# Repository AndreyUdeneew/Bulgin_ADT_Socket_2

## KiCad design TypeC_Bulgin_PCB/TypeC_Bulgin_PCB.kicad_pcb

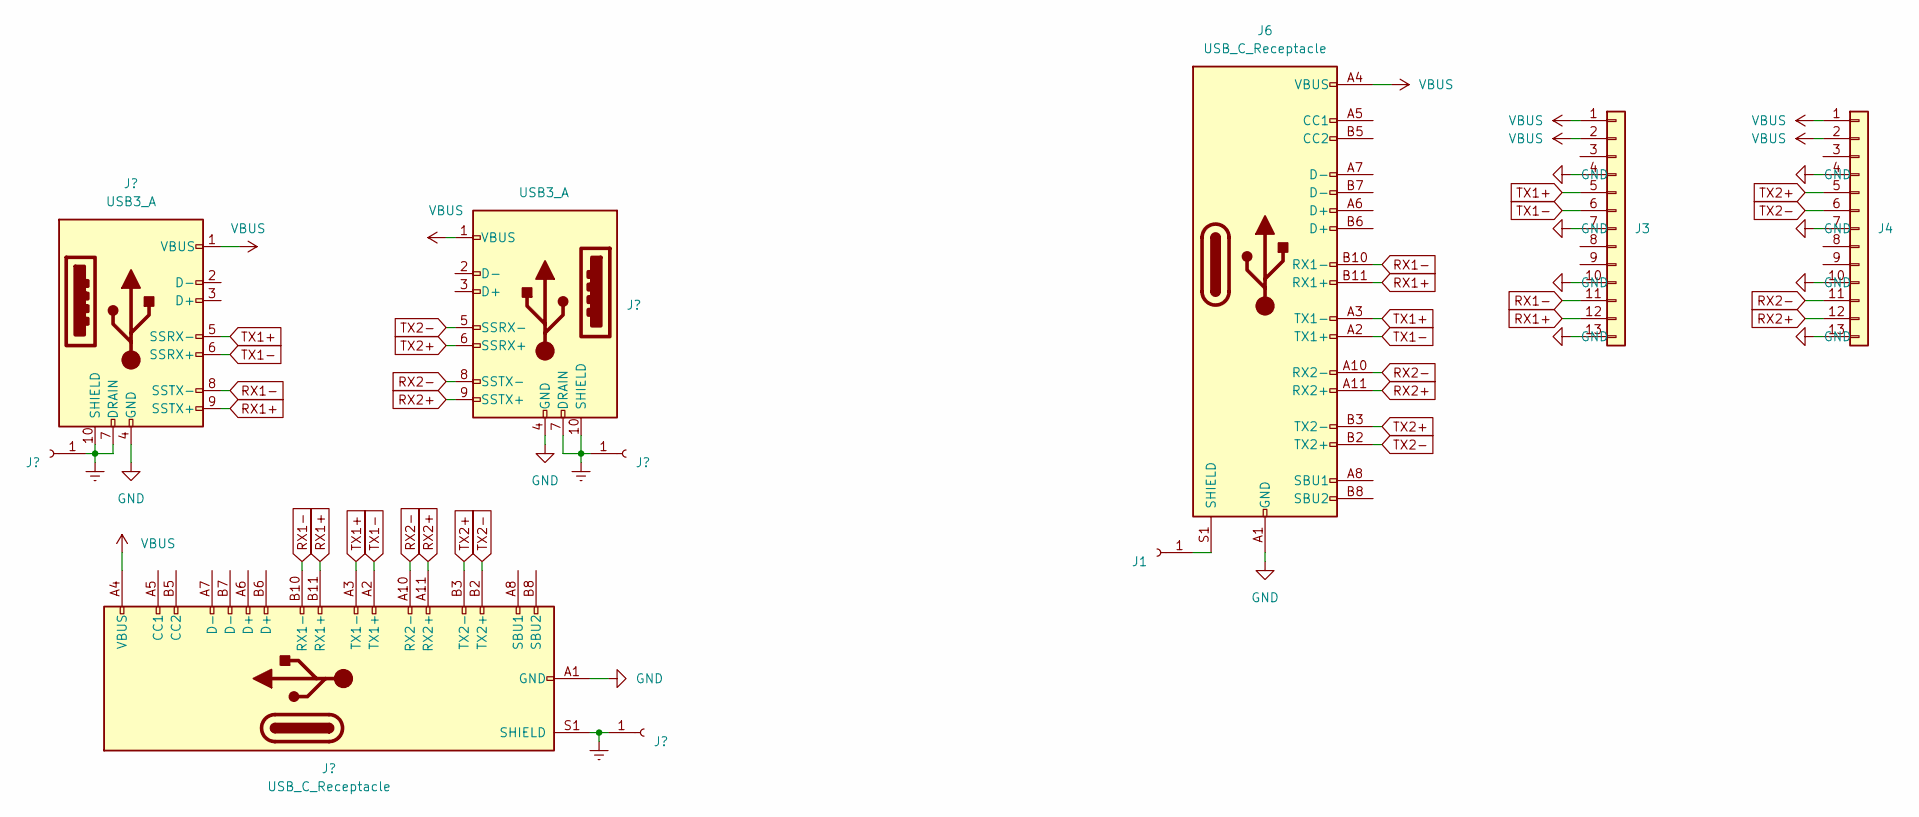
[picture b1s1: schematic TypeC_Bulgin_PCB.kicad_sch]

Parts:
J1: Conn_01x01_Female; PinHeader_1x01_P1.00mm_Vertical
J3, J4: Conn_01x13; ADT_13pin
J6: USB_C_Receptacle; USB_C_Receptacle_JAE_DX07S024WJ3R400

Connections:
GND: J3.4, J3.7, J3.10, J3.13, J4.4, J4.7, J4.10, J4.13, J6.A1 (GND), J6.A12 (GND), J6.B1 (GND), J6.B12 (GND)
unnamed: J1.1, J6.S1 (SHIELD)
RX1+: J3.12, J6.B11 (RX1+)
RX1-: J3.11, J6.B10 (RX1-)
RX2+: J4.12, J6.A11 (RX2+)
RX2-: J4.11, J6.A10 (RX2-)
TX1+: J3.5, J6.A3 (TX1-)
TX1-: J3.6, J6.A2 (TX1+)
TX2+: J4.5, J6.B3 (TX2-)
TX2-: J4.6, J6.B2 (TX2+)
VBUS: J3.1, J3.2, J4.1, J4.2, J6.A4 (VBUS), J6.A9 (VBUS), J6.B4 (VBUS), J6.B9 (VBUS)

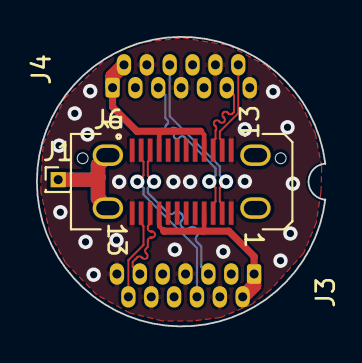
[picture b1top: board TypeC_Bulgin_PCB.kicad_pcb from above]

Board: 2 copper layers, 16.0 x 16.1 mm, 4 parts (0 on the bottom side), 11 nets.

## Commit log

2022-06-03 v0.1 universal TypeC connections were created
2022-06-03 v0.2 TXn were swapped
2022-06-04 v0.3 Seems 2B ready
2022-06-06 v0.4 key & axes were added
2022-06-06 v0.5 little changes
2022-06-06 v0.6 seems 2B ready
2022-06-06 v0.61 little changes
2022-06-06 v0.62 DRC errors were corrected, Gerbers, drl were updated
2022-06-06 v0.63 geometry was corrected, gerbers, DRC, drl
2022-06-24 v0.64 USB circuit was added
